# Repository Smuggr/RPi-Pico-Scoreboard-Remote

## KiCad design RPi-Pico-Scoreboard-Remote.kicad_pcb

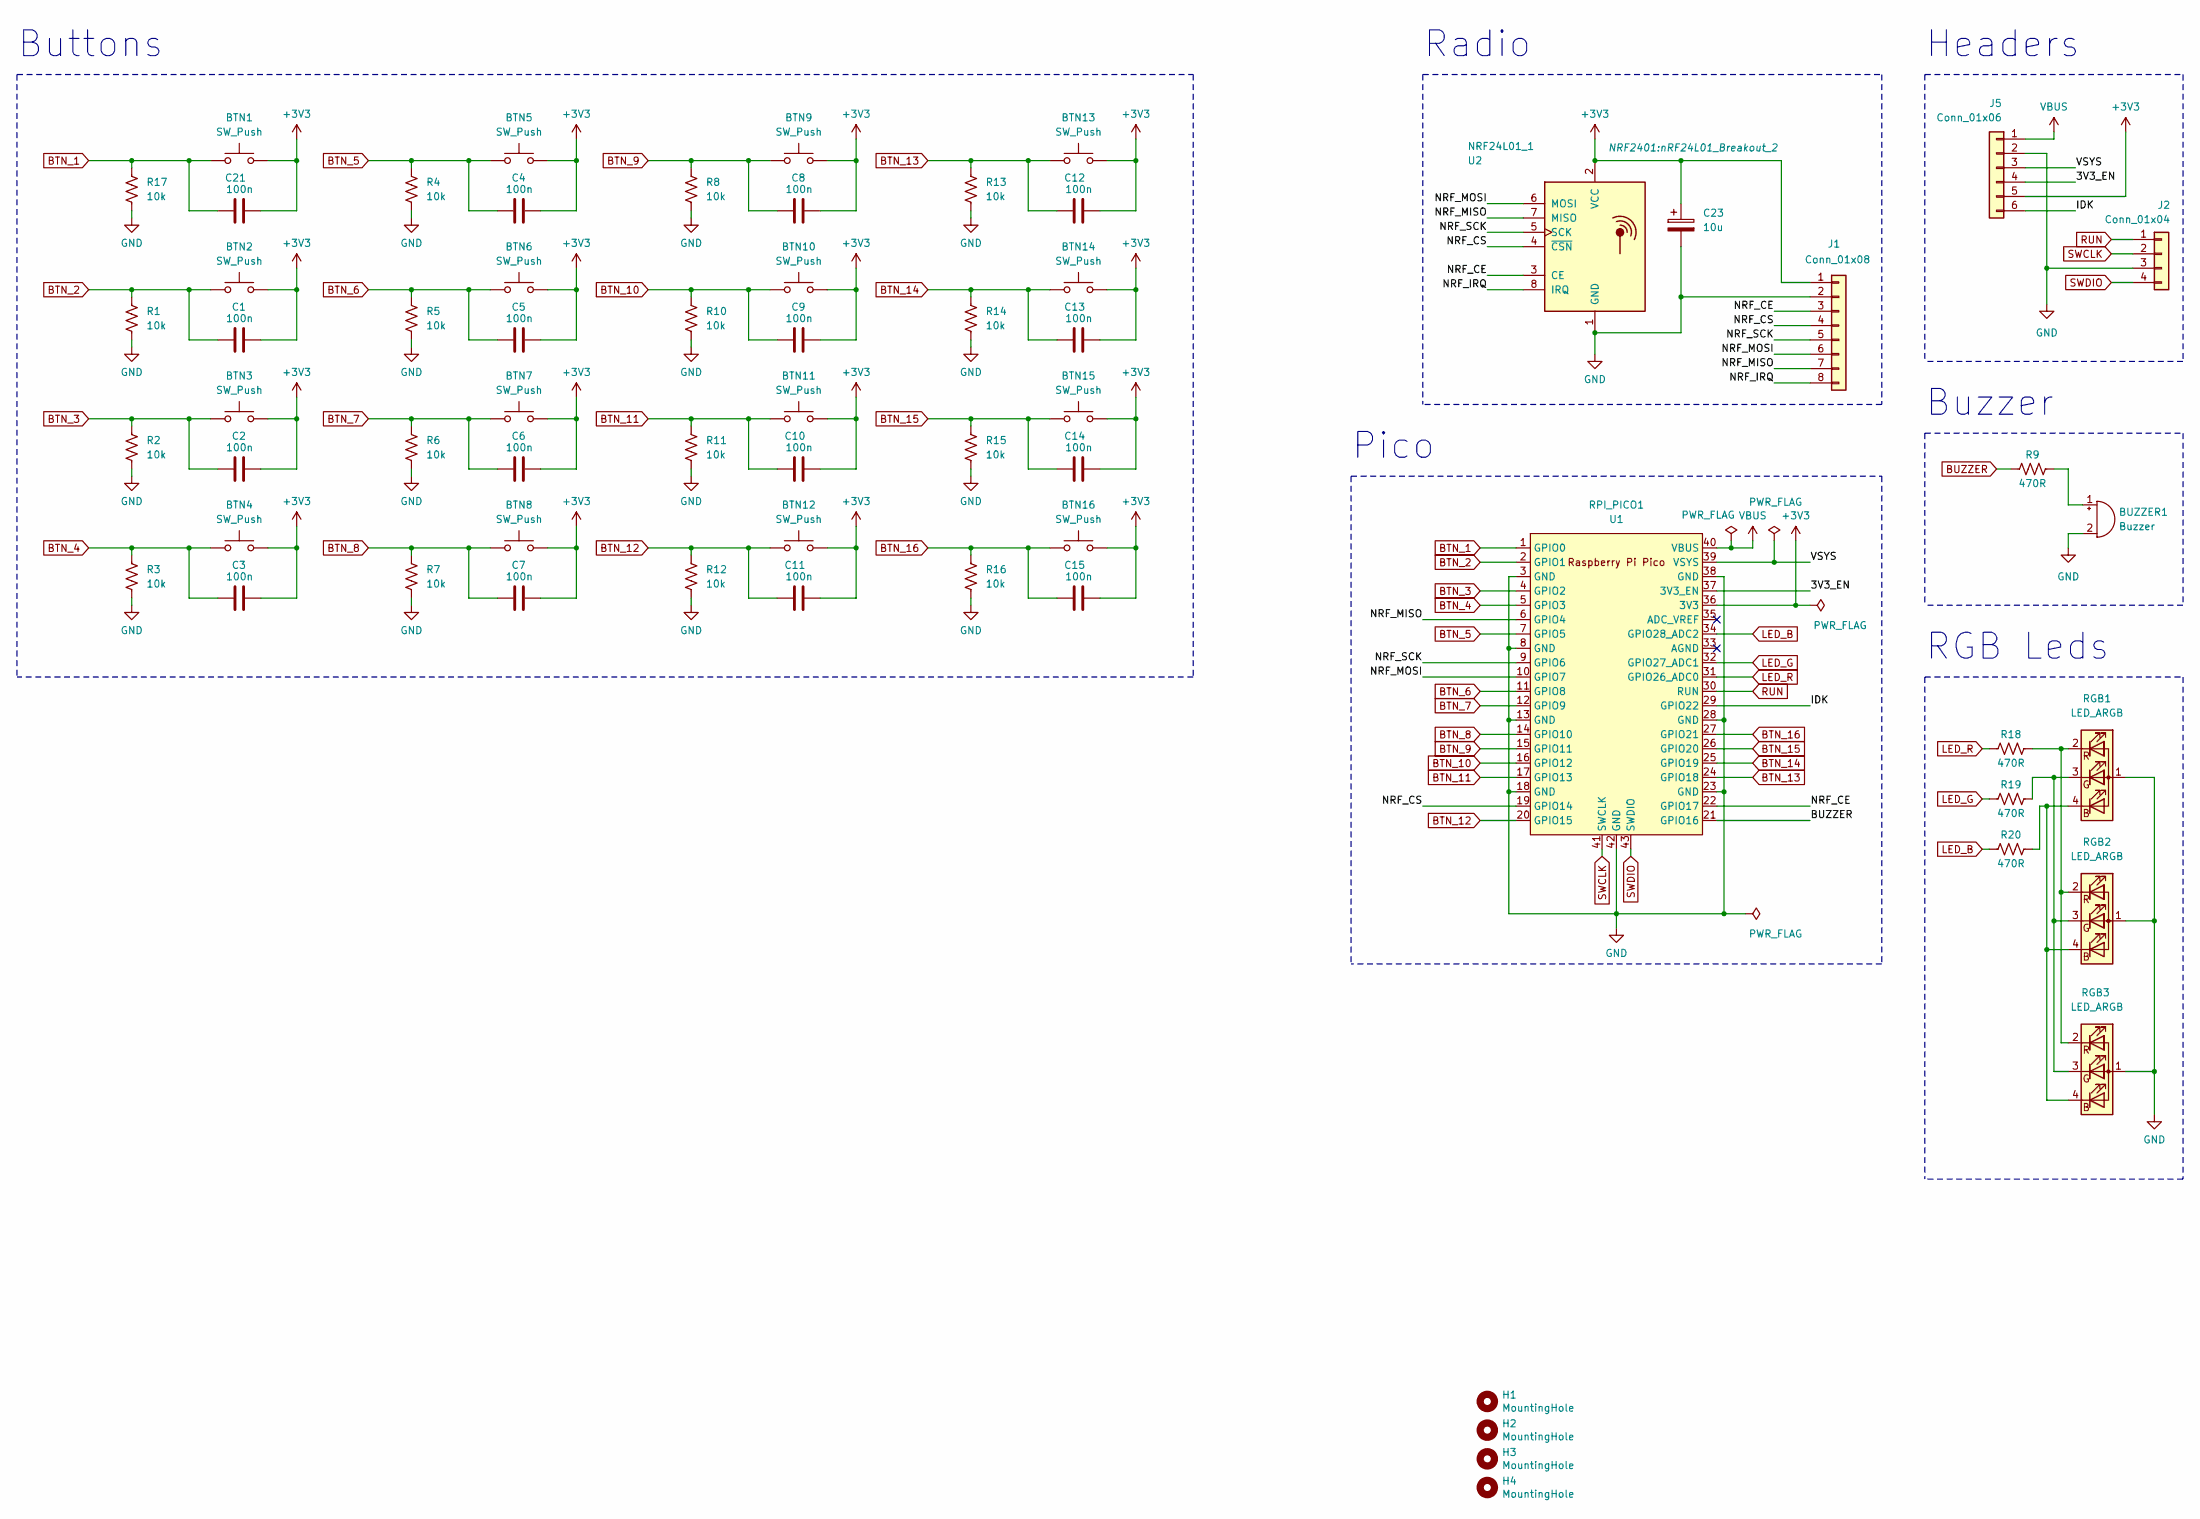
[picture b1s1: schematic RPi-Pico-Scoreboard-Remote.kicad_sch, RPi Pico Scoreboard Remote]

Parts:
BTN1, BTN2, BTN3, BTN4, BTN5, BTN6, BTN7, BTN8, BTN9, BTN10, BTN11, BTN12, BTN13, BTN14, BTN15, BTN16: SW_Push; SW_Push_1P1T_NO_6x6mm_H9.5mm
BUZZER1: Buzzer; Buzzer_12x9.5RM7.6
C1, C2, C3, C4, C5, C6, C7, C8, C9, C10, C11, C12, C13, C14, C15, C21: 100n; C_0201_0603Metric
C23: 10u; C_0402_1005Metric
H1, H2, H3, H4: MountingHole; MountingHole_2.7mm_Pad_TopBottom
J1: Conn_01x08; PinHeader_1x08_P1.27mm_Horizontal
J2: Conn_01x04; PinHeader_1x04_P2.54mm_Vertical
J5: Conn_01x06; PinHeader_1x06_P2.54mm_Vertical
NRF24L01_1: U2; nRF24L01_Breakout_2
R1, R2, R3, R4, R5, R6, R7, R8, R10, R11, R12, R13, R14, R15, R16, R17: 10k; R_0603_1608Metric
R9, R18, R19, R20: 470R; R_0402_1005Metric
RGB1, RGB3: LED_ARGB; LED_RGB_5050-6
RGB2: LED_ARGB; LED_D5.0mm-4_RGB_Wide_Pins
RPI_PICO1: U1; RPi_Pico_SMD_TH

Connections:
+3V3: BTN1.2, BTN2.2, BTN3.2, BTN4.2, BTN5.2, BTN6.2, BTN7.2, BTN8.2, BTN9.2, BTN10.2, BTN11.2, BTN12.2, BTN13.2, BTN14.2, BTN15.2, BTN16.2, C1.2, C2.2, C3.2, C4.2, C5.2, C6.2, C7.2, C8.2, C9.2, C10.2, C11.2, C12.2, C13.2, C14.2, C15.2, C21.2, C23.1, J1.1, J5.5, NRF24L01_1.2 (VCC), RPI_PICO1.36 (3V3)
/3V3_EN: J5.4, RPI_PICO1.37 (3V3_EN)
/IDK: J5.6, RPI_PICO1.29 (GPIO22)
/NRF_CE: J1.3, NRF24L01_1.3 (CE), RPI_PICO1.22 (GPIO17)
/NRF_CS: J1.4, NRF24L01_1.4 (~CSN), RPI_PICO1.19 (GPIO14)
/NRF_IRQ: J1.8, NRF24L01_1.8 (IRQ)
/NRF_MISO: J1.7, NRF24L01_1.7 (MISO), RPI_PICO1.6 (GPIO4)
/NRF_MOSI: J1.6, NRF24L01_1.6 (MOSI), RPI_PICO1.10 (GPIO7)
/NRF_SCK: J1.5, NRF24L01_1.5 (SCK), RPI_PICO1.9 (GPIO6)
/VSYS: J5.3, RPI_PICO1.39 (VSYS)
BTN_1: BTN1.1, C21.1, R17.1, RPI_PICO1.1 (GPIO0)
BTN_2: BTN2.1, C1.1, R1.1, RPI_PICO1.2 (GPIO1)
BTN_3: BTN3.1, C2.1, R2.1, RPI_PICO1.4 (GPIO2)
BTN_4: BTN4.1, C3.1, R3.1, RPI_PICO1.5 (GPIO3)
BTN_5: BTN5.1, C4.1, R4.1, RPI_PICO1.7 (GPIO5)
BTN_6: BTN6.1, C5.1, R5.1, RPI_PICO1.11 (GPIO8)
BTN_7: BTN7.1, C6.1, R6.1, RPI_PICO1.12 (GPIO9)
BTN_8: BTN8.1, C7.1, R7.1, RPI_PICO1.14 (GPIO10)
BTN_9: BTN9.1, C8.1, R8.1, RPI_PICO1.15 (GPIO11)
BTN_10: BTN10.1, C9.1, R10.1, RPI_PICO1.16 (GPIO12)
BTN_11: BTN11.1, C10.1, R11.1, RPI_PICO1.17 (GPIO13)
BTN_12: BTN12.1, C11.1, R12.1, RPI_PICO1.20 (GPIO15)
BTN_13: BTN13.1, C12.1, R13.1, RPI_PICO1.24 (GPIO18)
BTN_14: BTN14.1, C13.1, R14.1, RPI_PICO1.25 (GPIO19)
BTN_15: BTN15.1, C14.1, R15.1, RPI_PICO1.26 (GPIO20)
BTN_16: BTN16.1, C15.1, R16.1, RPI_PICO1.27 (GPIO21)
BUZZER: R9.1, RPI_PICO1.21 (GPIO16)
GND: BUZZER1.2 (-), C23.2, H1.1, H2.1, H3.1, H4.1, J1.2, J2.3, J5.2, NRF24L01_1.1 (GND), R1.2, R2.2, R3.2, R4.2, R5.2, R6.2, R7.2, R8.2, R10.2, R11.2, R12.2, R13.2, R14.2, R15.2, R16.2, R17.2, RGB1.1 (A), RGB2.1 (A), RGB3.1 (A), RPI_PICO1.3 (GND), RPI_PICO1.8 (GND), RPI_PICO1.13 (GND), RPI_PICO1.18 (GND), RPI_PICO1.23 (GND), RPI_PICO1.28 (GND), RPI_PICO1.38 (GND), RPI_PICO1.42 (GND)
LED_B: R20.1, RPI_PICO1.34 (GPIO28_ADC2)
LED_G: R19.1, RPI_PICO1.32 (GPIO27_ADC1)
LED_R: R18.1, RPI_PICO1.31 (GPIO26_ADC0)
unnamed: BUZZER1.1 (+), R9.2
unnamed: R20.2, RGB1.4 (BK), RGB2.4 (BK), RGB3.4 (BK)
unnamed: R19.2, RGB1.3 (GK), RGB2.3 (GK), RGB3.3 (GK)
unnamed: R18.2, RGB1.2 (RK), RGB2.2 (RK), RGB3.2 (RK)
RUN: J2.1, RPI_PICO1.30 (RUN)
SWCLK: J2.2, RPI_PICO1.41 (SWCLK)
SWDIO: J2.4, RPI_PICO1.43 (SWDIO)
VBUS: J5.1, RPI_PICO1.40 (VBUS)

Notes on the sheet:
Buzzer
Radio
Buttons
Pico
Headers
RGB Leds

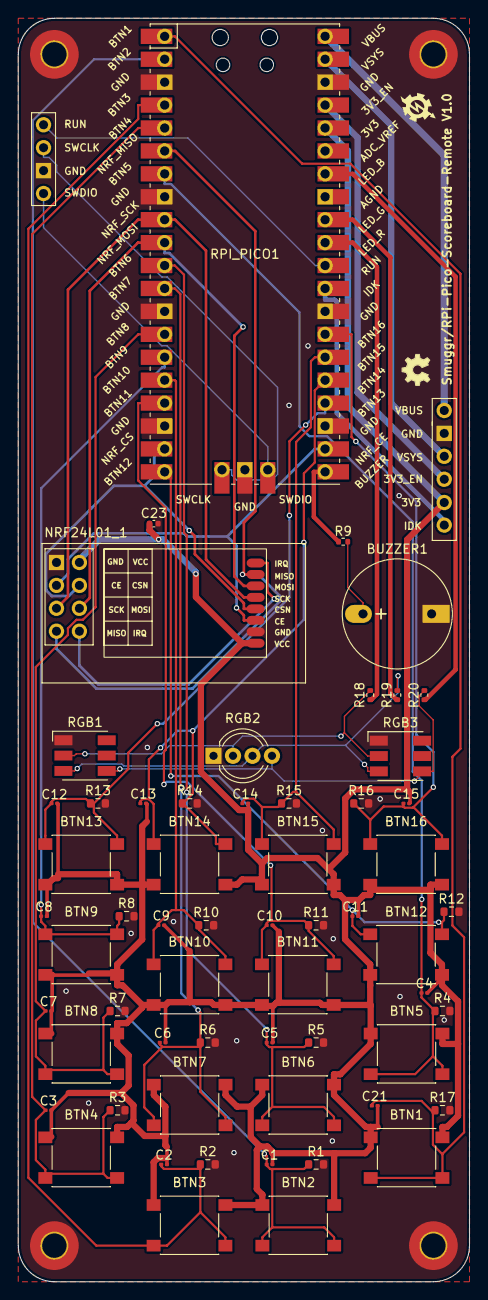
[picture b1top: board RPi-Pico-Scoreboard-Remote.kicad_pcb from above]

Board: 2 copper layers, 50.0 x 140.0 mm, 66 parts (0 on the bottom side), 39 nets.

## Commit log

2024-09-22 first revision of the board
2024-09-22 added backups to gitignore
2024-09-22 deleted RPi-Pico-Scoreboard-Remote-backups directory
